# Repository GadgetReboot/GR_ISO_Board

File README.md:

# GR_ISO_Board
Isolation breakout board with a 5V isolated DC-DC converter, optocouplers, Relay, and more.

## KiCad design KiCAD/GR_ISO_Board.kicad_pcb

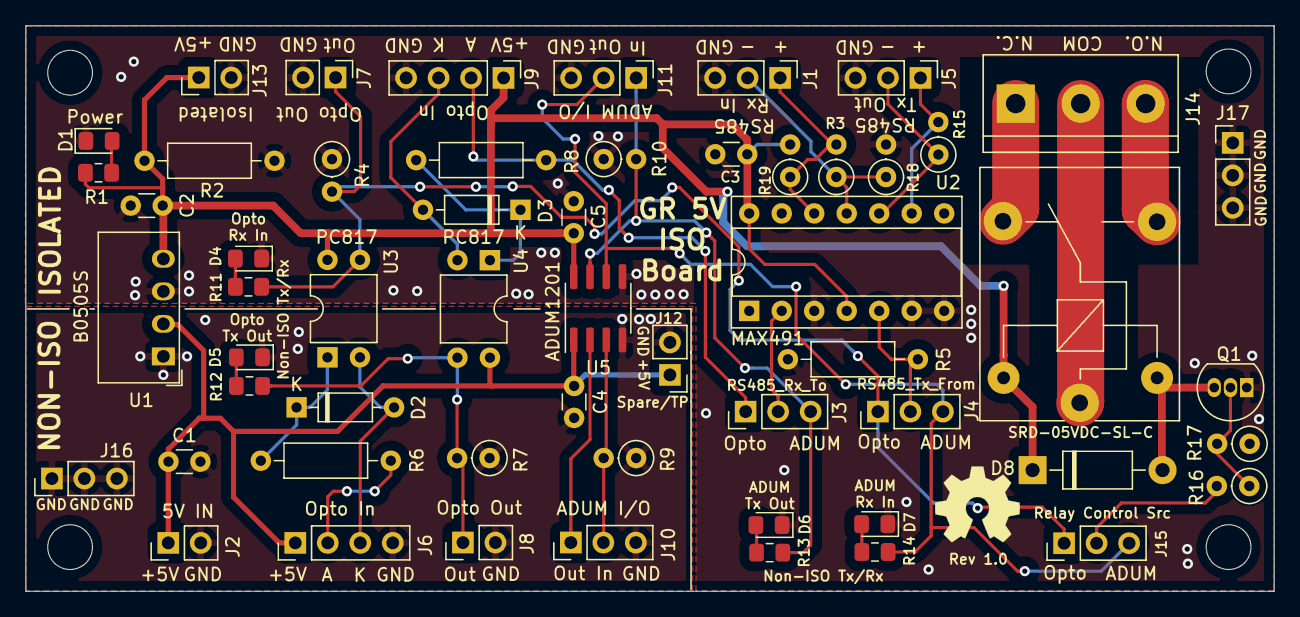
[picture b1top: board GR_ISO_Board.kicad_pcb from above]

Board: 2 copper layers, 97.6 x 44.2 mm, 56 parts (0 on the bottom side), 33 nets.

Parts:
C1, C2, C3, C4, C5: 100nF; C_Disc_D3.0mm_W1.6mm_P2.50mm
D1, D4, D5, D6, D7: LED_Small_ALT; LED_0805_2012Metric_Pad1.15x1.40mm_HandSolder
D2, D3: 1N4148; D_DO-35_SOD27_P7.62mm_Horizontal
D8: 1N4001; D_DO-41_SOD81_P10.16mm_Horizontal
J1, J3, J4, J5, J10, J11, J15, J16, J17: Conn_01x03; PinHeader_1x03_P2.54mm_Vertical
J2, J7, J8, J12, J13: Conn_01x02; PinHeader_1x02_P2.54mm_Vertical
J6, J9: Conn_01x04; PinHeader_1x04_P2.54mm_Vertical
J14: Screw_Terminal_01x03; TerminalBlock_bornier-3_P5.08mm
K1: SRD-05VDC-SL-C; Relay_SPDT_SANYOU_SRD_Series_Form_C
Q1: 2N3904; TO-92_Inline
R1, R11, R12, R13, R14: 1K; R_0805_2012Metric_Pad1.15x1.40mm_HandSolder
R2, R6, R8: 1K; R_Axial_DIN0207_L6.3mm_D2.5mm_P10.16mm_Horizontal
R3, R15: 120r; R_Axial_DIN0207_L6.3mm_D2.5mm_P2.54mm_Vertical
R4, R7, R9, R10, R17: 100K; R_Axial_DIN0207_L6.3mm_D2.5mm_P2.54mm_Vertical
R5: 100K; R_Axial_DIN0207_L6.3mm_D2.5mm_P10.16mm_Horizontal
R16: 1K; R_Axial_DIN0207_L6.3mm_D2.5mm_P2.54mm_Vertical
R18, R19: 4.7K; R_Axial_DIN0207_L6.3mm_D2.5mm_P2.54mm_Vertical
U1: B0505S; Converter_DCDC_muRata_CRE1xxxxxx3C_THT
U2: MAX491E; DIP-14_W7.62mm_Socket
U3, U4: PC817; DIP-4_W7.62mm
U5: ADuM1201AR; SOIC-8_3.9x4.9mm_P1.27mm

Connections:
+5V: C2.1, C3.1, C5.1, D8.1, J9.1, J13.1, K1.5, R1.2, R2.2, R19.2, U1.4, U2.4, U2.14, U3.4, U5.8
+5VD: C1.1, C4.1, J2.1, J6.1, J12.1, U1.2, U4.4, U5.1
/AD_IN: J3.3, J11.1, R10.2, R13.2, U5.7
/AD_OUT: J4.3, J11.2, J15.3, R14.2, U5.6
/OC1_LED: D2.2, J6.3, U3.2
/OC1_TR: J4.1, J7.1, J15.1, R4.2, R11.2, U3.3
/OC2_LED: J3.1, J9.2, R8.1
/OC2_TR: J8.1, R7.2, R12.2, U4.3
GND: C2.2, C3.2, C5.2, D1.1, D4.1, D6.1, D7.1, J1.3, J5.3, J7.2, J9.4, J11.3, J13.2, J17.1, J17.2, J17.3, Q1.1, R2.1, R4.1, R5.1, R10.1, R17.1, R18.2, U1.3, U2.3, U2.6, U2.7, U5.5
GNDREF: C1.2, C4.2, D5.1, J2.2, J6.4, J8.2, J10.3, J12.2, J16.1, J16.2, J16.3, R7.1, R9.1, U1.1, U5.4
unnamed: D1.2, R1.1
unnamed: D2.1, R6.1, U3.1
unnamed: D3.1, R8.2, U4.1
unnamed: D3.2, J9.3, U4.2
unnamed: D4.2, R11.1
unnamed: D5.2, R12.1
unnamed: D6.2, R13.1
unnamed: D7.2, R14.1
unnamed: D8.2, K1.2, Q1.3
unnamed: J1.1, R3.2, R19.1, U2.12
unnamed: J1.2, R3.1, R18.1, U2.11
unnamed: J3.2, U2.2
unnamed: J4.2, R5.2, U2.5
unnamed: J5.1, R15.2, U2.9
unnamed: J5.2, R15.1, U2.10
unnamed: J6.2, R6.2
unnamed: J10.1, U5.2
unnamed: J10.2, R9.2, U5.3
unnamed: J14.1, K1.4
unnamed: J14.2, K1.1
unnamed: J14.3, K1.3
unnamed: J15.2, R16.2
unnamed: Q1.2, R16.1, R17.2
